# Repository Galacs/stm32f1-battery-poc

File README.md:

# STM32F1 Battery POC

STM32F1 based pcb to test 3s Li-ion cells protection with 3 phases brushless and steppers driver interfaces.

## IC List

- STM32F103C8T (Main MCU)
- QRE1113 (reflectance sensor)
- HT753-1 (3v3 LDO)
- LM78M (5v LDO)
- DRV8311 (BLDC driver)
- DRV8424 (Stepper driver)
- BQ77905 (3S battery protection)
- SN65HVD (CAN transceiver)

## Top preview

## Preview 3d render

## Pictures

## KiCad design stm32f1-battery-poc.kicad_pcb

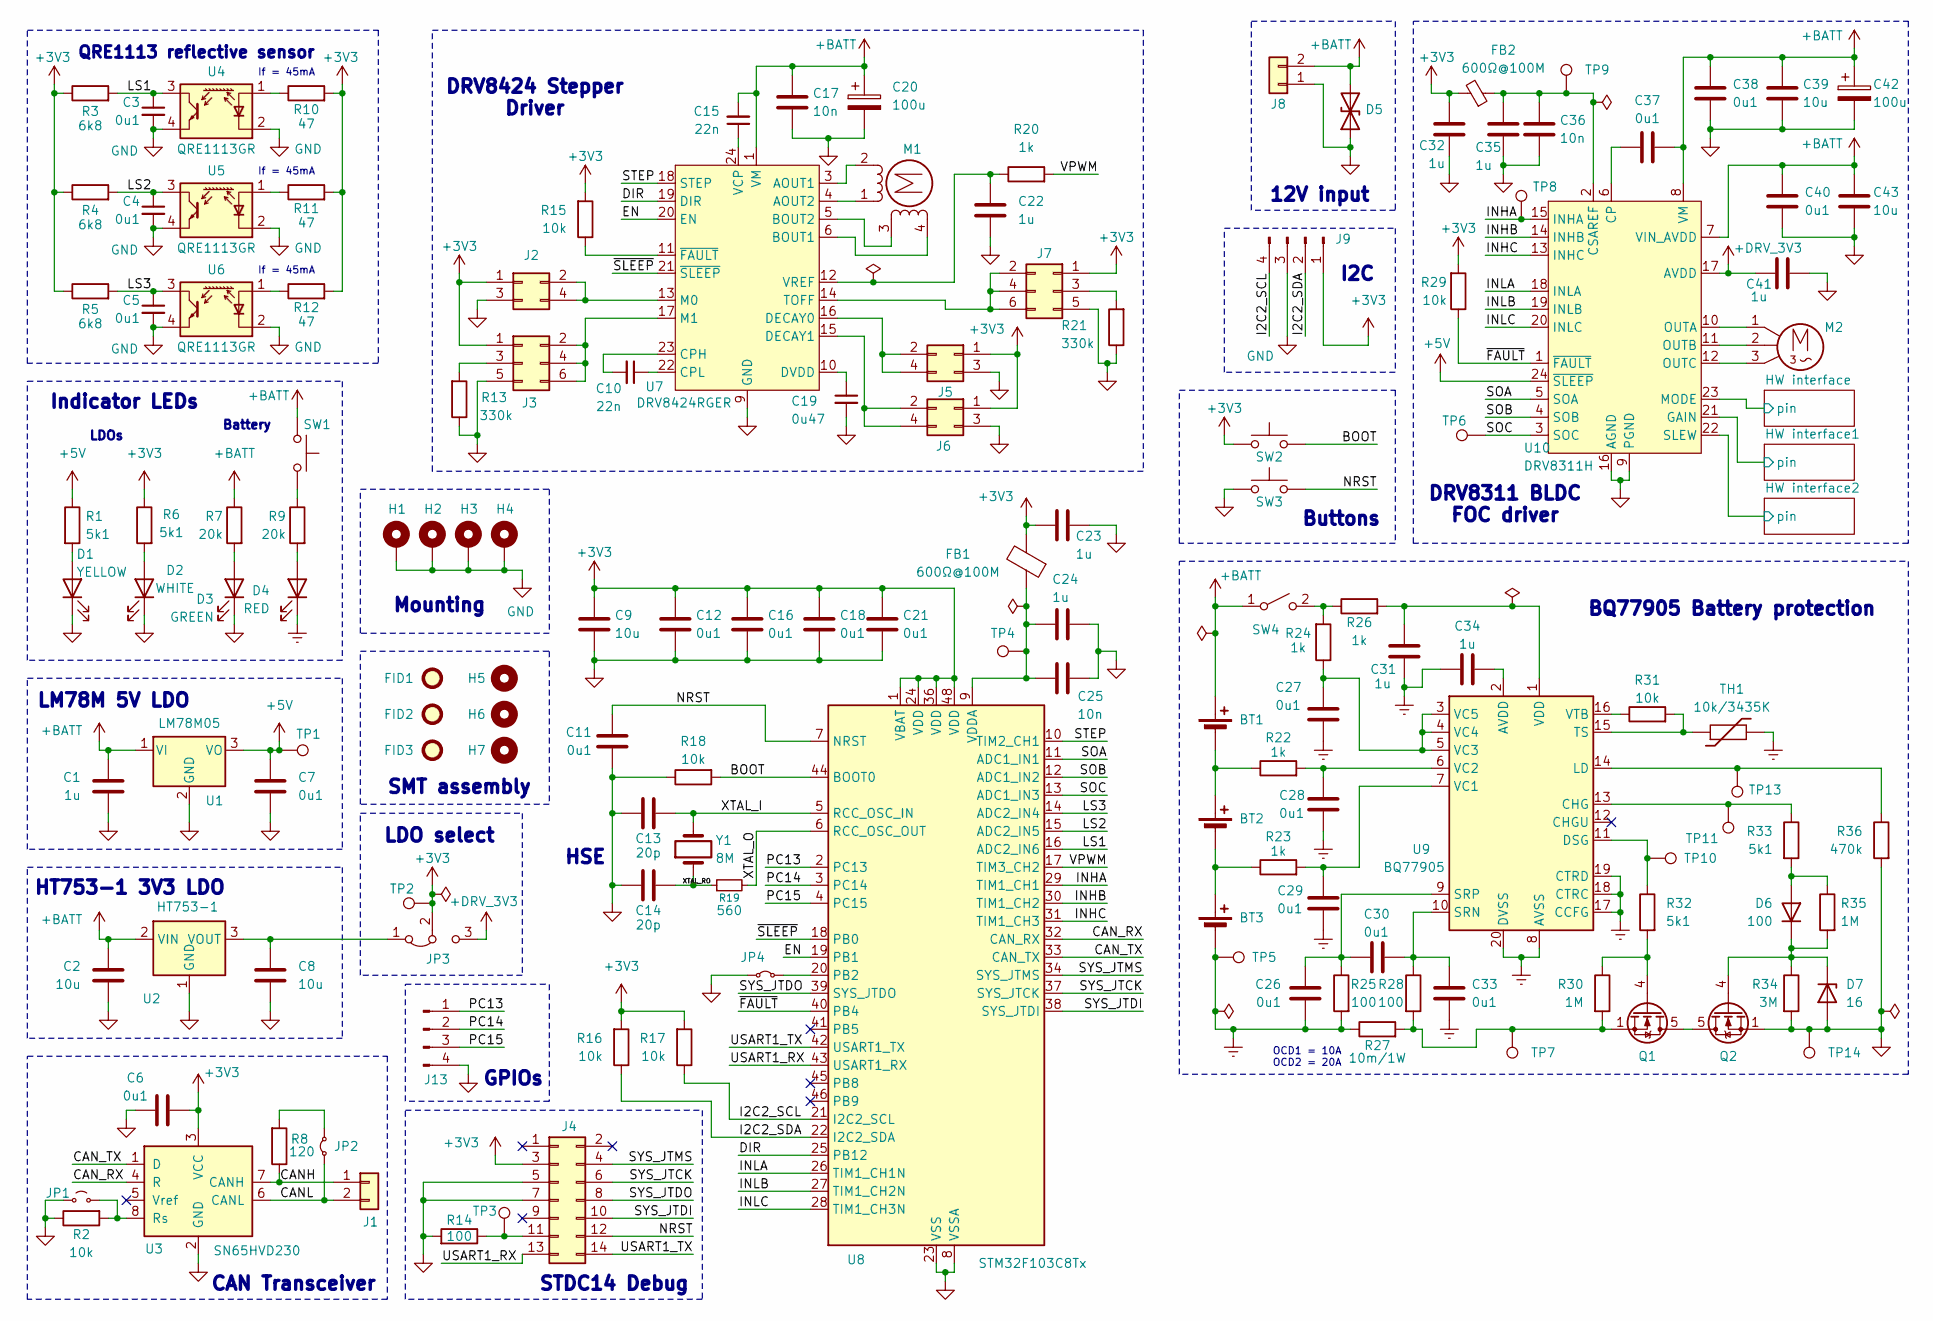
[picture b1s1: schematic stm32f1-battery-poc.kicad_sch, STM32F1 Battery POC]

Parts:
BT1, BT2, BT3: Battery_Cell; BatteryHolder_MYOUNG_BH-18650-B1BA002
C1, C22, C23, C24, C31, C32, C34, C35, C41: 1u; C_0402_1005Metric; Manufacturer Part Number CL05A105KA5NQNC; JLCPCB Part # C52923
C2, C8, C9, C39, C43: 10u; C_0805_2012Metric; Manufacturer Part Number GRM21BR61H106KE43L; JLCPCB Part # C440198
C3, C4, C5, C6, C7, C11, C12, C16, C18, C21, C26, C27, C28, C29, C30, C33, C37, C38, C40: 0u1; C_0402_1005Metric; Manufacturer Part Number CL05B104KB54PNC; JLCPCB Part # C307331
C10, C15: 22n; C_0402_1005Metric; Manufacturer Part Number 0402B223K500NT; JLCPCB Part # C1532
C13, C14: 20p; C_0603_1608Metric; Manufacturer Part Number CL10C200JB8NNNC; JLCPCB Part # C1648
C17, C25, C36: 10n; C_0402_1005Metric; Manufacturer Part Number CL05B103KB5NNNC; JLCPCB Part # C15195
C19: 0u47; C_0603_1608Metric; Manufacturer Part Number CL10B474KA8NNNC; JLCPCB Part # C1623
C20, C42: 100u; CP_Elec_6.3x7.7; Manufacturer Part Number EEEFTH101XAP; JLCPCB Part # C165974
D1: YELLOW; LED_0805_2012Metric; Manufacturer Part Number KT-0805Y; JLCPCB Part # C2296
D2: WHITE; LED_0603_1608Metric; Manufacturer Part Number KT-0603W; JLCPCB Part # C2290
D3: GREEN; LED_0805_2012Metric; Manufacturer Part Number KT-0805G; JLCPCB Part # C2297
D4: RED; LED_0603_1608Metric; Manufacturer Part Number KT-0603R; JLCPCB Part # C2286
D5: D_TVS; D_SMB; Manufacturer Part Number SMBJ30CA; JLCPCB Part # C2925441
D6: 100; D_SOD-323; Manufacturer Part Number 1N4148WS; JLCPCB Part # C2128
D7: 16; D_SOD-123; Manufacturer Part Number MMSZ5246B; JLCPCB Part # C19077429
FB1, FB2: 600Ω@100M; L_0805_2012Metric; Manufacturer Part Number GZ2012D101TF; JLCPCB Part # C1015
FID1, FID2, FID3: Fiducial; Fiducial_1mm_Mask2mm
H1, H2, H3, H4: MountingHole_Pad; MountingHole_2.2mm_M2_Pad_Via
H5, H6, H7: MountingHole; ToolingHole_1.152mm
J1: Conn_01x02; PinHeader_1x02_P2.54mm_Vertical
J2, J5, J6: Conn_02x02_Odd_Even; PinHeader_2x02_P1.27mm_Vertical_SMD
J3, J7: Conn_02x03_Odd_Even; PinHeader_2x03_P1.27mm_Vertical_SMD
J4: Conn_02x07_Odd_Even; PinHeader_2x07_P1.27mm_Vertical
J8: Conn_01x02; TerminalBlock_Phoenix_MKDS-1,5-2-5.08_1x02_P5.08mm_Horizont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
J9, J13: Conn_01x04_Pin; PinHeader_1x04_P2.54mm_Vertical
JP1: Jumper_2_Small_Open; PinHeader_2x01_P1.27mm_Vertical_SMD
JP2, JP4: Jumper_2_Small_Bridged; PinHeader_2x01_P1.27mm_Vertical_SMD
JP3: Jumper_3_Bridged12; PinHeader_1x03_P1.27mm_Vertical_SMD_Pin1Left
M1: Stepper_Motor_bipolar; JST_XH_S6B-XH-A_Stepper_1x06_P2.50mm_Horizontal
M2: Motor_3_Phases; PinHeader_1x03_P2.54mm_Vertical
Q1, Q2: Q_NMOS; Vishay_PowerPAK_1212-8_Single; Manufacturer Part Number SIS412DN-T1-GE3; JLCPCB Part # C111309
R1, R6, R32, R33: 5k1; R_0402_1005Metric; Manufacturer Part Number 0402WGF5101TCE; JLCPCB Part # C25905
R2, R15, R16, R17, R18, R29, R31: 10k; R_0402_1005Metric; Manufacturer Part Number 0402WGF1002TCE; JLCPCB Part # C25744
R3, R4, R5: 6k8; R_0603_1608Metric; Manufacturer Part Number 0603WAF6801T5E; JLCPCB Part # C23212
R7, R9: 20k; R_0603_1608Metric; Manufacturer Part Number 0603WAF2002T5E; JLCPCB Part # C4184
R8: 120; R_1206_3216Metric; Manufacturer Part Number 1206W4F1200T5E; JLCPCB Part # C17909
R10, R11, R12: 47; R_0603_1608Metric; Manufacturer Part Number 0603WAF470JT5E; JLCPCB Part # C23182
R13, R21: 330k; R_0603_1608Metric; Manufacturer Part Number 0603WAF3303T5E; JLCPCB Part # C23137
R14, R25, R28: 100; R_0402_1005Metric; Manufacturer Part Number 0402WGF1000TCE; JLCPCB Part # C25076
R19: 560; R_0603_1608Metric; Manufacturer Part Number 0603WAF5600T5E; JLCPCB Part # C23204
R20, R22, R23, R24, R26: 1k; R_0402_1005Metric; Manufacturer Part Number 0402WGF1001TCE; JLCPCB Part # C11702
R27: 10m/1W; R_1206_3216Metric; Manufacturer Part Number FMF06FTHR010-LH; JLCPCB Part # C105362
R30, R35: 1M; R_0402_1005Metric; Manufacturer Part Number 0402WGF1004TCE; JLCPCB Part # C26083
R34: 3M; R_0603_1608Metric; Manufacturer Part Number 0603WAF3004T5E; JLCPCB Part # C23156
R36: 470k; R_0603_1608Metric; Manufacturer Part Number 0603WAF4703T5E; JLCPCB Part # C23178
SW1, SW2, SW3: SW_Push; SW_SPST_TS-1088-xR020; Manufacturer Part Number TS-1088-AR02016; JLCPCB Part # C720477
SW4: SW_SPST; PinHeader_1x02_P2.54mm_Vertical
TH1: 10k/3435K; PinSocket_1x02_P2.54mm_Vertical
TP1, TP2, TP3, TP4, TP5, TP6, TP7, TP8, TP9, TP10, TP11, TP13, TP14: TestPoint; TestPoint_Pad_D2.0mm
U1: LM78M05; TO-252-2; Manufacturer Part Number LM78M05ACKTPRG; JLCPCB Part # C5145267
U2: HT753-1; SOT-89-3; Manufacturer Part Number HT7533-1; JLCPCB Part # C14289
U3: SN65HVD230; SOIC-8_3.9x4.9mm_P1.27mm; Manufacturer Part Number SN65HVD230DR; JLCPCB Part # C12084
U4, U5, U6: QRE1113GR; OnSemi_CASE100CY; Manufacturer Part Number QRE1113GR; JLCPCB Part # C232862
U7: DRV8424RGER; Texas_RGE0024B_VQFN-24-1EP_4x4mm_P0.5mm_EP2.5x2.5mm_Thermal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; Manufacturer Part Number DRV8424RGER; JLCPCB Part # C1518725
U8: STM32F103C8Tx; LQFP-48_7x7mm_P0.5mm; Manufacturer Part Number STM32F103C8T6; JLCPCB Part # C8734
U9: BQ77905; TSSOP-20_4.4x6.5mm_P0.65mm; Manufacturer Part Number BQ7790509PWR; JLCPCB Part # C2866527
U10: DRV8311H; Texas_RRW0024A_WQFN-24-1EP_2x2mm_P0.4mmThermalVias; Manufacturer Part Number DRV8311HRRWR; JLCPCB Part # C5218862
Y1: 8M; Crystal_SMD_5032-2Pin_5.0x3.2mm; Manufacturer Part Number X50328MSB2GI; JLCPCB Part # C115962

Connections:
+3V3: C6.1, C9.1, C12.1, C16.1, C18.1, C21.1, C23.1, C32.1, FB1.2, FB2.2, J2.1, J3.1, J4.3, J5.1, J6.1, J7.1, J9.1, JP3.2 (C), R3.1, R4.1, R5.1, R6.1, R10.2, R11.2, R12.2, R15.2, R16.2, R17.2, R29.2, SW2.1, TP2.1, U3.3 (VCC), U8.1 (VBAT), U8.24 (VDD), U8.36 (VDD), U8.48 (VDD); also elsewhere on the board
+5V: C7.1, R1.1, TP1.1, U1.3 (VO), U10.24 (~SLEEP)
+BATT: BT1.1 (+), C1.1, C2.1, C15.2, C17.1, C20.1, C37.2, C38.2, C39.2, C40.2, C42.1, C43.2, D5.2 (A2), J8.2, R7.1, SW1.2, SW4.1 (A), U1.1 (VI), U2.2 (VIN), U7.1 (VM), U7.8 (VM), U10.7 (VIN_AVDD), U10.8 (VM)
+DRV_3V3: C41.1, JP3.3 (B), U10.17 (AVDD)
/BOOT: R18.2, SW2.2, U8.44 (BOOT0)
/CANH: J1.1, R8.1, U3.7 (CANH)
/CANL: J1.2, JP2.1 (A), U3.6 (CANL)
/CAN_RX: U3.4 (R), U8.32 (CAN_RX)
/CAN_TX: U3.1 (D), U8.33 (CAN_TX)
/DIR: U7.19 (DIR), U8.25 (PB12)
/EN: U7.20 (EN), U8.19 (PB1)
/HW interface1/pin: U10.21 (GAIN); also elsewhere on the board
/HW interface2/pin: U10.22 (SLEW); also elsewhere on the board
/HW interface/pin: U10.23 (MODE); also elsewhere on the board
/I2C2_SCL: J9.4, R17.1, U8.21 (I2C2_SCL)
/I2C2_SDA: J9.2, R16.1, U8.22 (I2C2_SDA)
/INHA: TP8.1, U8.29 (TIM1_CH1), U10.15 (INHA)
/INHB: U8.30 (TIM1_CH2), U10.14 (INHB)
/INHC: U8.31 (TIM1_CH3), U10.13 (INHC)
/INLA: U8.26 (TIM1_CH1N), U10.18 (INLA)
/INLB: U8.27 (TIM1_CH2N), U10.19 (INLB)
/INLC: U8.28 (TIM1_CH3N), U10.20 (INLC)
/LS1: C3.1, R3.2, U4.3, U8.16 (ADC2_IN6)
/LS2: C4.1, R4.2, U5.3, U8.15 (ADC2_IN5)
/LS3: C5.1, R5.2, U6.3, U8.14 (ADC2_IN4)
/NRST: C11.1, J4.12, SW3.2, U8.7 (NRST)
/PC13: J13.1, U8.2 (PC13)
/PC14: J13.2, U8.3 (PC14)
/PC15: J13.3, U8.4 (PC15)
/SOA: U8.11 (ADC1_IN1), U10.5 (SOA)
/SOB: U8.12 (ADC1_IN2), U10.4 (SOB)
/SOC: TP6.1, U8.13 (ADC1_IN3), U10.3 (SOC)
/STEP: U7.18 (STEP), U8.10 (TIM2_CH1)
/SYS_JTCK: J4.6, U8.37 (SYS_JTCK)
/SYS_JTDI: J4.10, U8.38 (SYS_JTDI)
/SYS_JTDO: J4.8, U8.39 (SYS_JTDO)
/SYS_JTMS: J4.4, U8.34 (SYS_JTMS)
/USART1_RX: J4.13, U8.43 (USART1_RX)
/USART1_TX: J4.14, U8.42 (USART1_TX)
/VPWM: R20.2, U8.17 (TIM3_CH2)
/XTAL_I: C13.1, U8.5 (RCC_OSC_IN), Y1.2
/XTAL_O: R19.2, U8.6 (RCC_OSC_OUT)
/XTAL_RO: C14.1, R19.1, Y1.1
/~FAULT: R29.1, U8.40 (PB4), U10.1 (~FAULT)
/~SLEEP: U7.21 (~SLEEP), U8.18 (PB0)
BGND: BT3.2 (-), C26.2, C27.2, C28.2, C29.2, C31.1, C33.2, C34.2, D4.1 (K), R25.2, R27.1, TH1.2, TP5.1, U9.8 (AVSS), U9.17 (CCFG), U9.18 (CTRC), U9.19 (CTRD), U9.20 (DVSS)
GND: C1.2, C2.2, C3.2, C4.2, C5.2, C6.2, C7.2, C8.2, C9.2, C11.2, C12.2, C13.2, C14.2, C16.2, C17.2, C18.2, C19.2, C20.2, C21.2, C22.2, C23.2, C24.2, C25.2, C32.2, C35.2, C36.2, C38.1, C39.1, C40.1, C41.2, C42.2, C43.1, D1.1 (K), D2.1 (K), D3.1 (K), D5.1 (A1), D7.2 (A), H1.1, H2.1, H3.1, H4.1, J2.3, J3.5, J4.5, J4.7, J5.3, J6.3, J7.5, J8.1, J9.3, J13.4, JP1.1 (A), JP4.1 (A), Q2.1 (S), Q2.2 (S), Q2.3 (S), R2.1, R13.1, R14.2, R18.1, R21.1, R34.2, R36.2, SW3.1, TP14.1, U1.2 (GND), U2.1 (GND), U3.2 (GND), U4.2 (K), U4.4, U5.2 (K), U5.4, U6.2 (K), U6.4, U7.2 (PGND), U7.7 (PGND), U7.9 (GND), U7.25 (GND), U8.8 (VSSA), U8.23 (VSS), U8.35 (VSS), U8.47 (VSS), U10.9 (PGND), U10.16 (AGND), U10.25 (EPAD); also elsewhere on the board
unnamed: BT1.2 (-), BT2.1 (+), R22.1
unnamed: BT2.2 (-), BT3.1 (+), R23.1
unnamed: D1.2 (A), R1.2
unnamed: D2.2 (A), R6.2
unnamed: D3.2 (A), R7.2
unnamed: D4.2 (A), R9.2
unnamed: D6.2 (A), R33.2, R35.1
unnamed: D6.1 (K), D7.1 (K), Q2.4 (G), R34.1, R35.2
unnamed: J2.2, J2.4, U7.13 (M0)
unnamed: J3.2, J3.4, J3.6, U7.17 (M1)
unnamed: J3.3, R13.2
unnamed: J4.11, R14.1, TP3.1
unnamed: J5.2, J5.4, U7.16 (DECAY0)
unnamed: J6.2, J6.4, U7.15 (DECAY1)
unnamed: J7.2, J7.4, J7.6, U7.14 (TOFF)
unnamed: J7.3, R21.2
unnamed: JP1.2 (B), R2.2, U3.8 (Rs)
unnamed: JP2.2 (B), R8.2
unnamed: C8.1, JP3.1 (A), U2.3 (VOUT)
unnamed: JP4.2 (B), U8.20 (PB2)
unnamed: M1.2 (-), U7.3 (AOUT1)
unnamed: Q1.5 (D), Q2.5 (D)
unnamed: Q1.4 (G), R30.1, R32.2
unnamed: Q1.1 (S), Q1.2 (S), Q1.3 (S), R27.2, R28.2, R30.2, TP7.1
unnamed: R9.1, SW1.1
unnamed: R24.2, R26.1, SW4.2 (B)
unnamed: R10.1, U4.1 (A)
unnamed: R11.1, U5.1 (A)
unnamed: R12.1, U6.1 (A)
unnamed: M1.1, U7.4 (AOUT2)
unnamed: M1.4, U7.6 (BOUT1)
unnamed: M1.3, U7.5 (BOUT2)
unnamed: C10.2, U7.23 (CPH)
unnamed: C10.1, U7.22 (CPL)
unnamed: C19.1, U7.10 (DVDD)
unnamed: C15.1, U7.24 (VCP)
unnamed: C22.1, R20.1, U7.12 (VREF)
unnamed: R15.1, U7.11 (~FAULT)
unnamed: C24.1, C25.1, FB1.1, TP4.1, U8.9 (VDDA)
unnamed: C34.1, U9.2 (AVDD)
unnamed: R33.1, TP11.1, U9.13 (CHG)
unnamed: R32.1, TP10.1, U9.11 (DSG)
unnamed: R36.1, TP13.1, U9.14 (LD)
unnamed: C30.1, C33.1, R28.1, U9.10 (SRN)
unnamed: C26.1, C30.2, R25.1, U9.9 (SRP)
unnamed: R31.2, TH1.1, U9.15 (TS)
unnamed: C29.1, R23.2, U9.7 (VC1)
unnamed: C28.1, R22.2, U9.6 (VC2)
unnamed: C27.1, R24.1, U9.3 (VC5), U9.4 (VC4), U9.5 (VC3)
unnamed: C31.2, R26.2, U9.1 (VDD)
unnamed: R31.1, U9.16 (VTB)
unnamed: C37.1, U10.6 (CP)
unnamed: C35.1, C36.1, FB2.1, TP9.1, U10.2 (CSAREF)
unnamed: M2.1, U10.10 (OUTA)
unnamed: M2.2, U10.11 (OUTB)
unnamed: M2.3, U10.12 (OUTC)

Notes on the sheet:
Buttons
If = 45mA
LDOs
BQ77905 Battery protection
QRE1113 reflective sensor
SMT assembly
DRV8424 Stepper Driver
LDO select
LM78M 5V LDO
HSE
DRV8311 BLDC FOC driver
GPIOs
OCD1 = 10A OCD2 = 20A
STDC14 Debug
12V input
Mounting
Battery
I2C
HT753-1 3V3 LDO
Indicator LEDs
CAN Transceiver

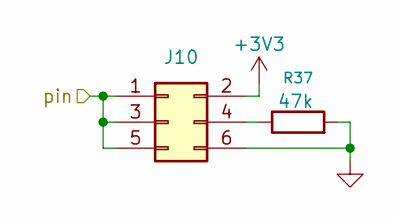
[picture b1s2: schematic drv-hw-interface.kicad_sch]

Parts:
J10: Conn_02x03_Odd_Even; PinHeader_2x03_P1.27mm_Vertical_SMD
R37: 47k; R_0402_1005Metric; Manufacturer Part Number 0402WGF4702TCE; JLCPCB Part # C25792

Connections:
+3V3: J10.2; also elsewhere on the board
/HW interface/pin: J10.1, J10.3, J10.5; also elsewhere on the board
GND: J10.6, R37.2; also elsewhere on the board
unnamed: J10.4, R37.1

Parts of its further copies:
J11, J12: Conn_02x03_Odd_Even; PinHeader_2x03_P1.27mm_Vertical_SMD
R38, R39: 47k; R_0402_1005Metric; Manufacturer Part Number 0402WGF4702TCE; JLCPCB Part # C25792

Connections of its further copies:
+3V3: J11.2, J12.2; also elsewhere on the board
/HW interface1/pin: J11.1, J11.3, J11.5; also elsewhere on the board
/HW interface2/pin: J12.1, J12.3, J12.5; also elsewhere on the board
GND: J11.6, J12.6, R38.2, R39.2; also elsewhere on the board
unnamed: J11.4, R38.1
unnamed: J12.4, R39.1

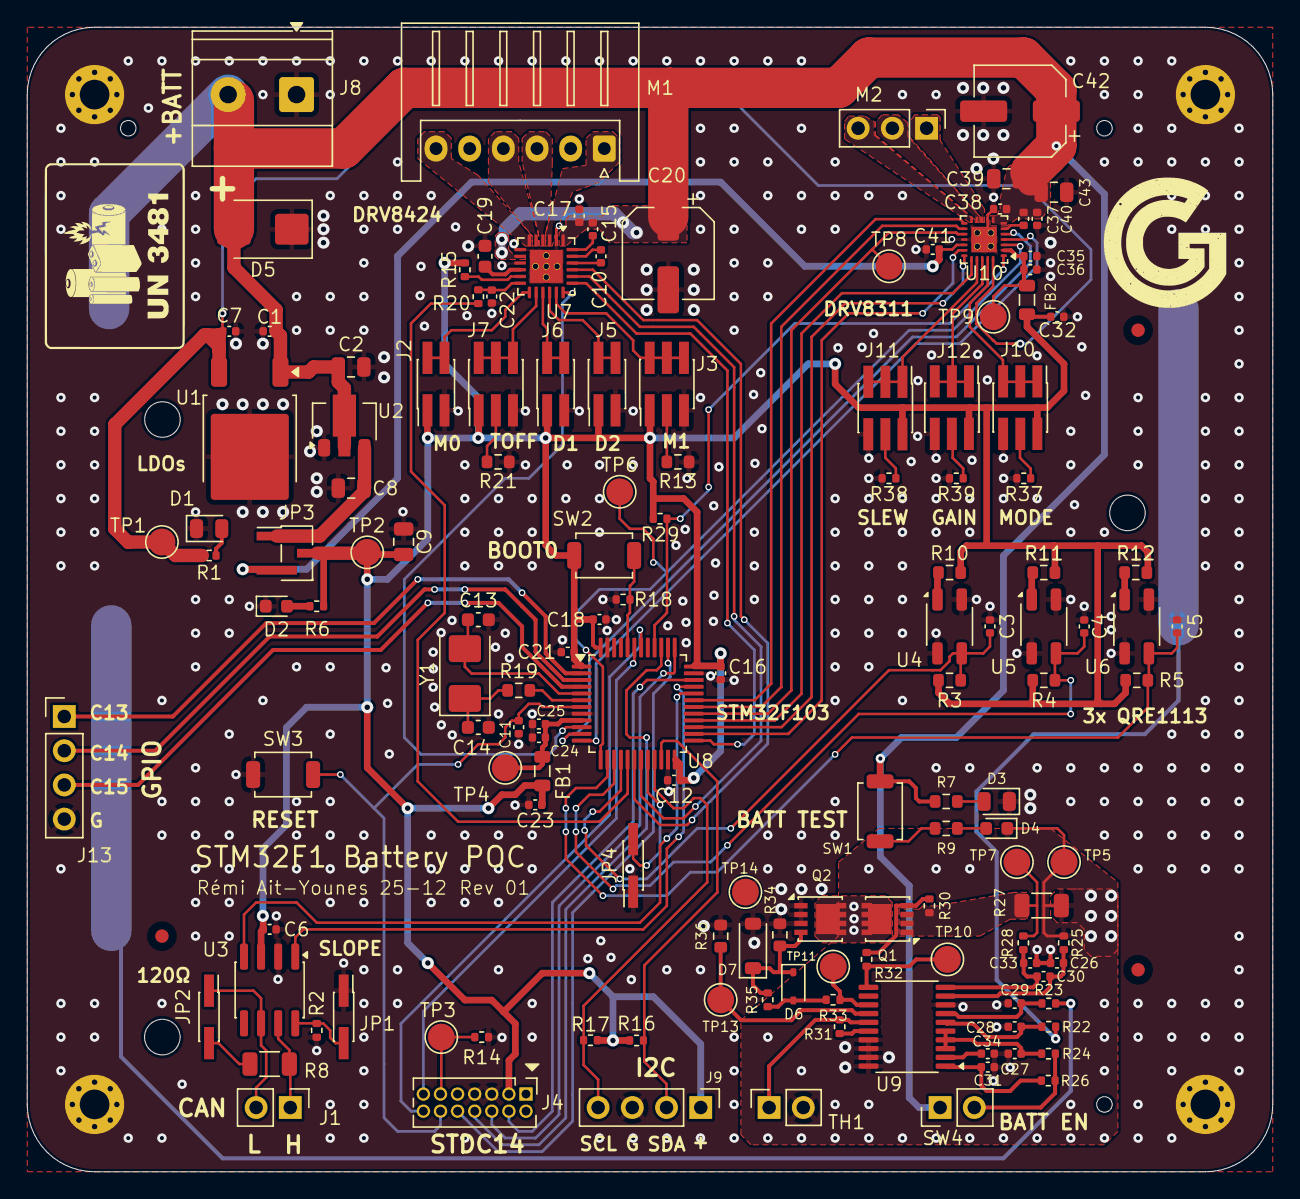
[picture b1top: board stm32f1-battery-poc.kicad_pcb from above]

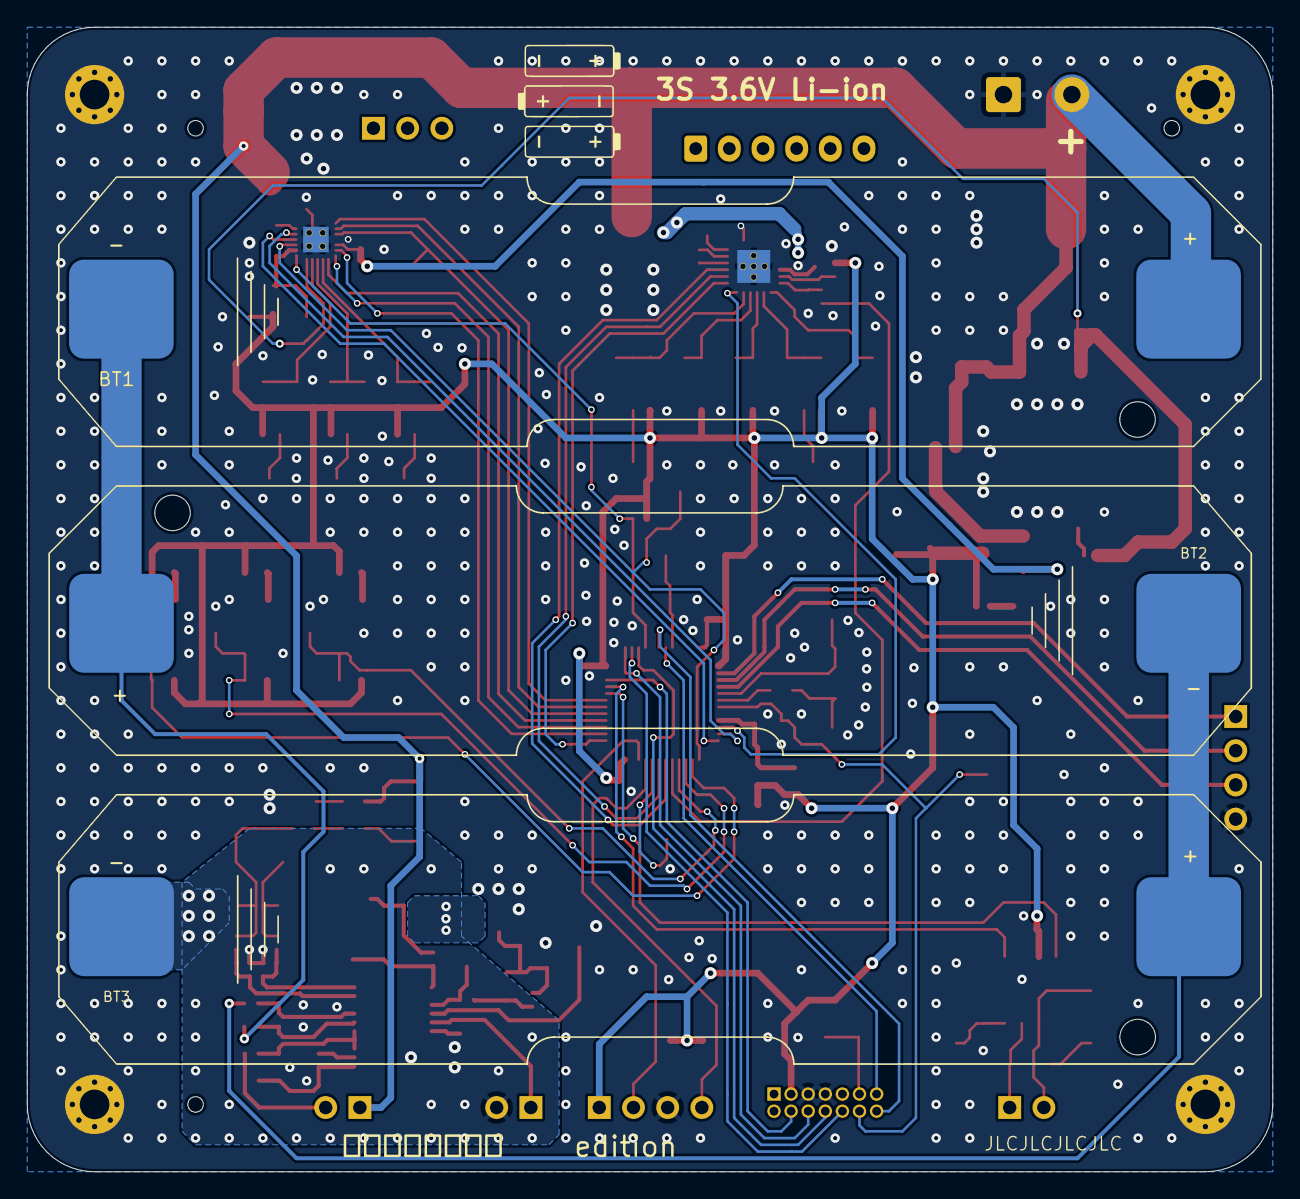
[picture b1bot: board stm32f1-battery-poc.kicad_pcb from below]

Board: 4 copper layers, 92.5 x 85.0 mm, 154 parts (3 on the bottom side), 106 nets.

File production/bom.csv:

Designator,Footprint,Quantity,Value,LCSC Part #
"C1, C22, C23, C24, C31, C32, C34, C35, C41",0402,9,1u,C52923
"C10, C15",0402,2,22n,C1532
"C11, C12, C16, C18, C21, C26, C27, C28, C29, C3, C30, C33, C37, C38, C4, C40, C5, C6, C7",0402,19,0u1,C307331
"C13, C14",0603,2,20p,C1648
"C17, C25, C36",0402,3,10n,C15195
C19,0603,1,0u47,C1623
"C2, C39, C43, C8, C9",0805,5,10u,C440198
"C20, C42",CP_Elec_6.3x7.7,2,100u,C165974
D1,0805,1,YELLOW,C2296
D2,0603,1,WHITE,C2290
D3,0805,1,GREEN,C2297
D4,0603,1,RED,C2286
D5,D_SMB,1,D_TVS,C2925441
D6,D_SOD-323,1,100,C2128
D7,D_SOD-123,1,16,C19077429
"FB1, FB2",0805,2,600Ω@100M,C1015
"Q1, Q2",Vishay_PowerPAK_1212-8_Single,2,Q_NMOS,C111309
"R1, R32, R33, R6",0402,4,5k1,C25905
"R10, R11, R12",0603,3,47,C23182
"R13, R21",0603,2,330k,C23137
"R14, R25, R28",0402,3,100,C25076
"R15, R16, R17, R18, R2, R29, R31",0402,7,10k,C25744
R19,0603,1,560,C23204
"R20, R22, R23, R24, R26",0402,5,1k,C11702
R27,1206,1,10m/1W,C105362
"R3, R4, R5",0603,3,6k8,C23212
"R30, R35",0402,2,1M,C26083
R34,0603,1,3M,C23156
R36,0603,1,470k,C23178
"R37, R38, R39",0402,3,47k,C25792
"R7, R9",0603,2,20k,C4184
R8,1206,1,120,C17909
"SW1, SW2, SW3",SW_SPST_TS-1088-xR020,3,SW_Push,C720477
U1,TO-252-2,1,LM78M05,C5145267
U10,Texas_RRW0024A_WQFN-24-1EP_2x2mm_P0.4mmThermalVias,1,DRV8311H,C5218862
U2,SOT-89-3,1,HT753-1,C14289
U3,SOIC-8_3.9x4.9mm_P1.27mm,1,SN65HVD230,C12084
"U4, U5, U6",OnSemi_CASE100CY,3,QRE1113GR,C232862
U7,Texas_RGE0024B_VQFN-24-1EP_4x4mm_P0.5mm_EP2.5x2.5mm_ThermalVias,1,DRV8424RGER,C1518725
U8,LQFP-48_7x7mm_P0.5mm,1,STM32F103C8Tx,C8734
U9,TSSOP-20_4.4x6.5mm_P0.65mm,1,BQ77905,C2866527
Y1,Crystal_SMD_5032-2Pin_5.0x3.2mm,1,8M,C115962

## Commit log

2025-12-06 schem: add STM32F103C8T6 symbol
2025-12-06 schem: add decoupling capacitors
2025-12-06 schem: add BOOT0 pulldown
2025-12-06 pcb: add BOOT and RST buttons
2025-12-06 schem: add 8Mhz HSE
2025-12-07 schem: add STDC14 Debug port
2025-12-07 schem: add SN65HVD230 CAN transceiver
2025-12-07 schem: add BQ77905 Battery protection
2025-12-07 schem: add battery cells to BQ77905
2025-12-07 schem: add FB to VDDA
2025-12-08 schem: add power indicator LEDs
2025-12-08 schem: add BQ77905 enable switch
2025-12-08 schem: add BQ77905 rsense filter
2025-12-08 schem: add LM78M 5V LDO
2025-12-08 schem: add HT753-1 3V3 LDO
2025-12-08 schem: reorganization
2025-12-08 schem: add 3V3 ldo select
2025-12-08 schem: add 12V power input
2025-12-08 schem: add DRV8311 bldc driver
2025-12-09 schem: add DRV8311 hardware pin config jumpers
2025-12-09 schem: import QRE1113 reflective sensor from motor-power-poc
2025-12-09 schem: add BQ77905 shunt resistor value
2025-12-09 schem: clean up LDO select
2025-12-09 schem: add DRV8311 missing power inputs
2025-12-10 schem: add DRV8311 nSLEEP pullup
2025-12-10 schem: connect DRV8311 to MCU
2025-12-11 schem: connect QRE1113 to MCU
2025-12-11 schem: add HSE external components values
2025-12-12 schem: add NCs to MCU
2025-12-12 schem: add test points
2025-12-12 schem: add title
2025-12-12 schem: add net classes
2025-12-12 schem: run and fix ERC
2025-12-12 schem: reannotate
2025-12-12 schem: regorganize to leave space for DRV8424RGER
2025-12-12 schem: add DRV8424RGER stepper driver
2025-12-12 schem: add DRV8424 mode setting jumpers
2025-12-20 schem: add I2C connector
2025-12-20 schema: connect DRV8424 vref pin
2025-12-21 schem: add footprints and ordering info to BOM
2025-12-21 schem: add missing DRV8424 MCU connections
2025-12-21 schem: renumber schematic
2025-12-21 schem: fix symbols orientations
2025-12-21 pcb: create file
2025-12-21 pbb: import stackup and constraints
2025-12-21 pcb: import footprints from schematic
2025-12-21 pcb: add missing 3d models
2025-12-21 pcb: initial rough layout
2025-12-21 schem/pcb: add fiducials, mounting and tooling holes
2025-12-21 schem/pcb: change jumpers to smd
2025-12-21 pcb: initial placement
2025-12-21 pcb: add holes layout
2025-12-21 pcb: add board outline
2025-12-21 pcb: refine connectors positions
2025-12-21 pcb: add grid/drill origin
2025-12-21 pcb: add gnd planes
2025-12-21 pcb: update net classes colors
2025-12-21 pcb: add gnd vias
2025-12-21 schem: change I2C pins
2025-12-21 pcb: add CAN layout
2025-12-21 pcb: add STDC14 debug port routing
2025-12-21 pcb: add CAN routing
2025-12-21 pcb: add DRV8311 routing
2025-12-21 pcb: add BQ77905 routing
2025-12-21 pcb: add DRV8424 stepper driver routing
2025-12-21 pcb: add I2C connector routing
2025-12-21 pcb: add power ldos routing
2025-12-21 pcb: add 3v3 power routing
2025-12-21 pcb: add QRE1113 routing
2025-12-21 pcb: add NRST routing
2025-12-21 pcb: add 5V routnig
2025-12-21 pcb: add missing connections
2025-12-21 schem/pcb: add spare gpio routing
2025-12-21 pcb: add stitching vias
2025-12-21 pcb: remove unused pads
2025-12-21 pcb(silkscreen): clean reference designators
2025-12-21 pcb(silkscreen): add user text
2025-12-21 pcb: run and fix DRC
2025-12-22 schem/pcb: update QRE1113 led resistors for 40mA
2025-12-23 pcb: remove unused internal pads
2025-12-23 pcb(silkscreen): replace placeholder
2025-12-23 pcb: add title
2025-12-23 add fabrication files
2026-02-10 add README.md
2026-02-10 add can transceiver to readme
2026-02-10 docs: add pictures to README
